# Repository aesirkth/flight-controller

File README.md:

# Flight Controller <!-- omit in toc -->

This is the embedded software on the Flight Controller for the project Mjollnir. The Flight Controller is on-board the rocket. The Flight Controller communicates with the ground through a radio link during all phases of the flight

The mission objectives for the Mjollnir project relevant to the electronics are the following:

**Primary objectives**

- **E.PO.1** Monitor the rocket while it is on the launchpad and give a “Go”/”No go” signal
- **E.PO.2** Control the rocket while it is on the launchpad
- **E.PO.3** Trigger the drogue parachute’s ejection after apogee
- **E.PO.4** Trigger the main parachute’s ejection before touchdown
- **E.PO.5** Support rocket recovery operations
- **E.PO.6** Record video footage from the rocket

**Secondary objectives**

- **E.SO.1** Send real-time telemetry from the rocket
- **E.SO.2** Receive & display real-time telemetry from the rocket at the Ground Station as long as the rocket is at a reasonable distance
- **E.SO.3** Send real-time video from the rocket
- **E.SO.4** Receive & display real-time video from the rocket at the Ground Station as long as the rocket is at a reasonable distance
- **E.SO.5** Acquire flight data with more sensors than those deemed “mission-critical”
- **E.SO.6** Store all flight data on-board the rocket for further analysis

All of them apply to some extent to the Flight Controller

# Table of content <!-- omit in toc -->

- [Description](#description)
  - [Hardware](#hardware)
  - [Software](#software)
    - [Installation](#installation)
  - [Tests](#tests)
- [Data protocol](#data-protocol)
- [Folder structure](#folder-structure)

# Description

## Hardware

The Flight Controller is a single PCB with power management, sensors, radio communication, and driver for the actuators used during the flight.

It has the following features:

- Dual microcontroller (main + backup)
- Low power long range LoRa transceiver
- Telemetry output via serial link (x3)
- GNSS support via serial link (x3)
- Compatible with 10 dof breakout board with MS5611 pressure sensors and MPU9250 IMU (2x)
- Compatible with K type thermocouples (2x)
- Flash memory
- EEDs driver for parachute ejection, with ESD protection + visual and audible warning (2x)
- RGB leds to display the board status
- Serial link to FPV transmitter
- CAN Bus

A more detailed description of the hardware is given in [doc/hardware_description.md](doc/hardware_description.md)

## Software

This repository uses [PlatformIO](https://platformio.org/) as the development tool for the two microcontrollers on the Flight Controller.

### Installation

1. Install [PlatformIO Core](https://docs.platformio.org/en/latest/core/index.html) or [PlatformIO IDE](https://platformio.org/install/ide) on your computer
2. Clone this repository
3. [Linux] install [udev](https://docs.platformio.org/en/latest/faq.html?highlight=99#platformio-udev-rules) rules

## Tests

See [test/](test/)

# Data protocol

The protocol to communicate between the Ground Station and the Rocket is detailed in [doc/data_protocol](doc/data_protocol.md)

# Folder structure

```
.
├── doc/
│   ├── img/
│   ├── diagrams/
│   ├── sources
│   |   └── flight_controller_v1.0.pdf
│   ├── data_protocol.md
│   └── hardware_description.md
├── include/
│   ├── hardware_definition_nano.h
│   └── hardware_definition_teensy.h
├── src/                                    // Code folder
│   └── test_companion_teensy.cpp           // Use with hardware_test_teensy
├── test/                                   // Unit tests
│   ├── hardware_test_nano/
│   ├── hardware_test_teensy/
│   └── README.md                           // Documentation for the tests
├── env_nano.ini                            // Extra platformIO config
├── env_teensy.ini                          // Extra platformIO config
├── LICENSE
├── platformio.ini                          // PlatformIO config
└── README.md                               // This file
```

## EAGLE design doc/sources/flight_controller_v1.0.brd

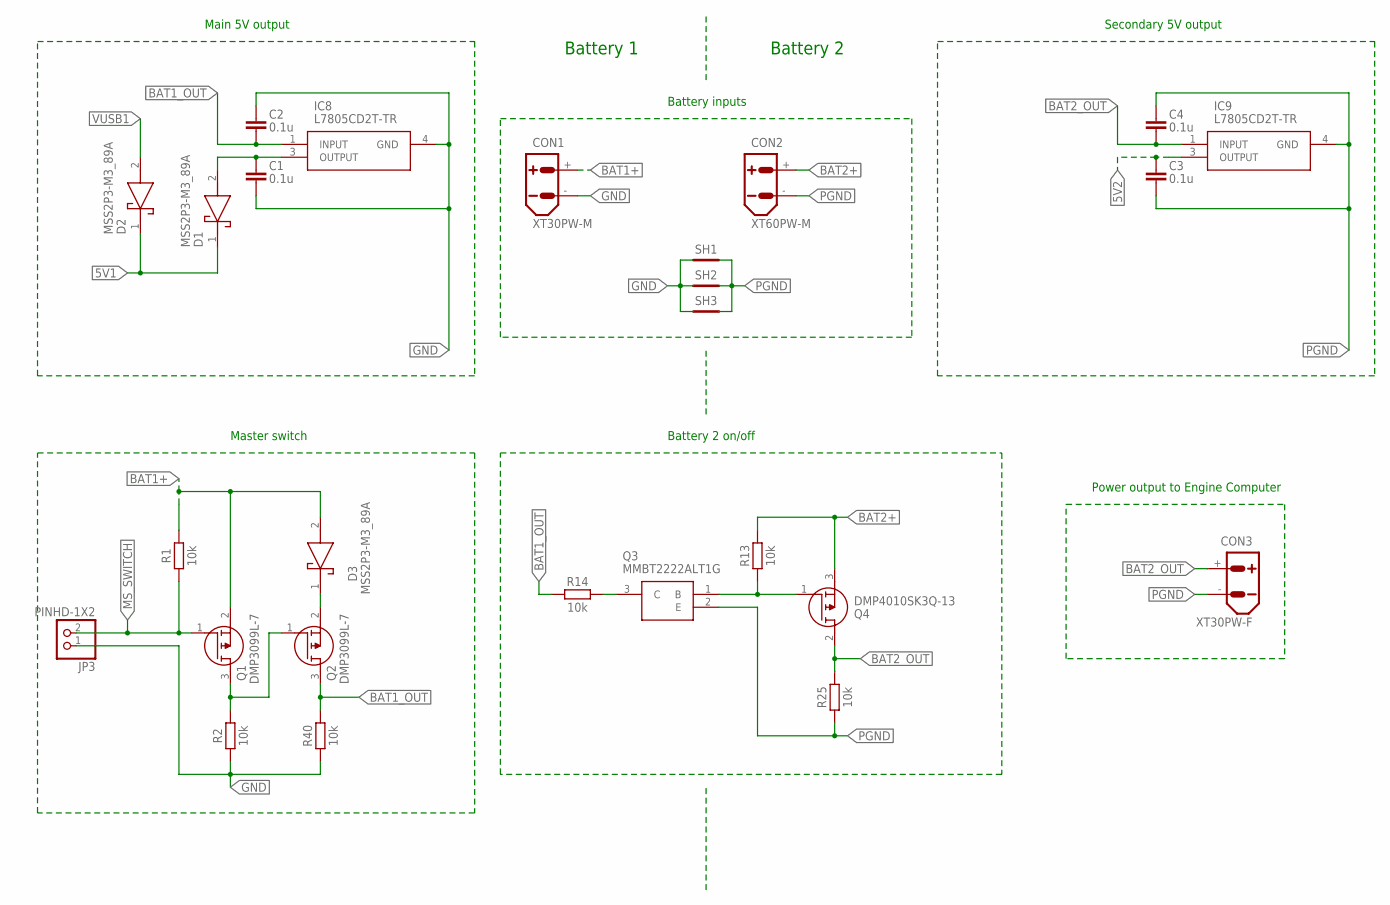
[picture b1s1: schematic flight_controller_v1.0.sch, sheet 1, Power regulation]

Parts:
C1, C2, C3, C4: 0.1u; CAPC2012X110
CON1: XT30PW-M
CON2: XT60PW-M
CON3: XT30PW-F
D1, D2, D3: MSS2P3-M3_89A; MSS2P3M389A
IC8, IC9: L7805CD2T-TR; TO254P1542X460-3N
JP3: PINHD-1X2; 1X02
Q1, Q2: DMP3099L-7; SOT96P240X120-3N
Q3: MMBT2222ALT1G; SOT96P237X111-3N
Q4: DMP4010SK3Q-13; SBR6100CTL13
R1, R2, R13, R14, R25, R40: 10k; RESC2012X65
SH1, SH2, SH3: SHORT-HT5; SHORT_TOP-50

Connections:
5V1: D1.1 (K), D2.1 (K); also elsewhere on the board
5V2: C3.1, IC9.3 (OUTPUT); also elsewhere on the board
BAT1+: CON1.+, D3.2 (A), Q1.2 (S), R1.2
BAT1_OUT: C2.2, IC8.1 (INPUT), Q2.3 (D), R14.1, R40.2; also elsewhere on the board
BAT2+: CON2.+, Q4.3 (S), R13.2
BAT2_OUT: C4.2, CON3.+, IC9.1 (INPUT), Q4.2 (D), R25.2; also elsewhere on the board
GND: C1.2, C2.1, CON1.-, IC8.4 (GND), JP3.1, R2.1, R40.1, SH1.1, SH2.1, SH3.1; also elsewhere on the board
MS_SWITCH: JP3.2, Q1.1 (G), R1.1; also elsewhere on the board
unnamed: Q1.3 (D), Q2.1 (G), R2.2
unnamed: Q3.1 (B), Q4.1 (G), R13.1
unnamed: Q3.3 (C), R14.2
unnamed: C1.1, D1.2 (A), IC8.3 (OUTPUT)
unnamed: D3.1 (K), Q2.2 (S)
PGND: C3.2, C4.1, CON2.-, CON3.-, IC9.4 (GND), Q3.2 (E), R25.1, SH1.2, SH2.2, SH3.2; also elsewhere on the board
VUSB1: D2.2 (A); also elsewhere on the board

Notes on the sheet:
Main 5V output
Battery inputs
Master switch
Secondary 5V output
Battery 2 on/off
Battery 1
Battery 2
Power output to Engine Computer

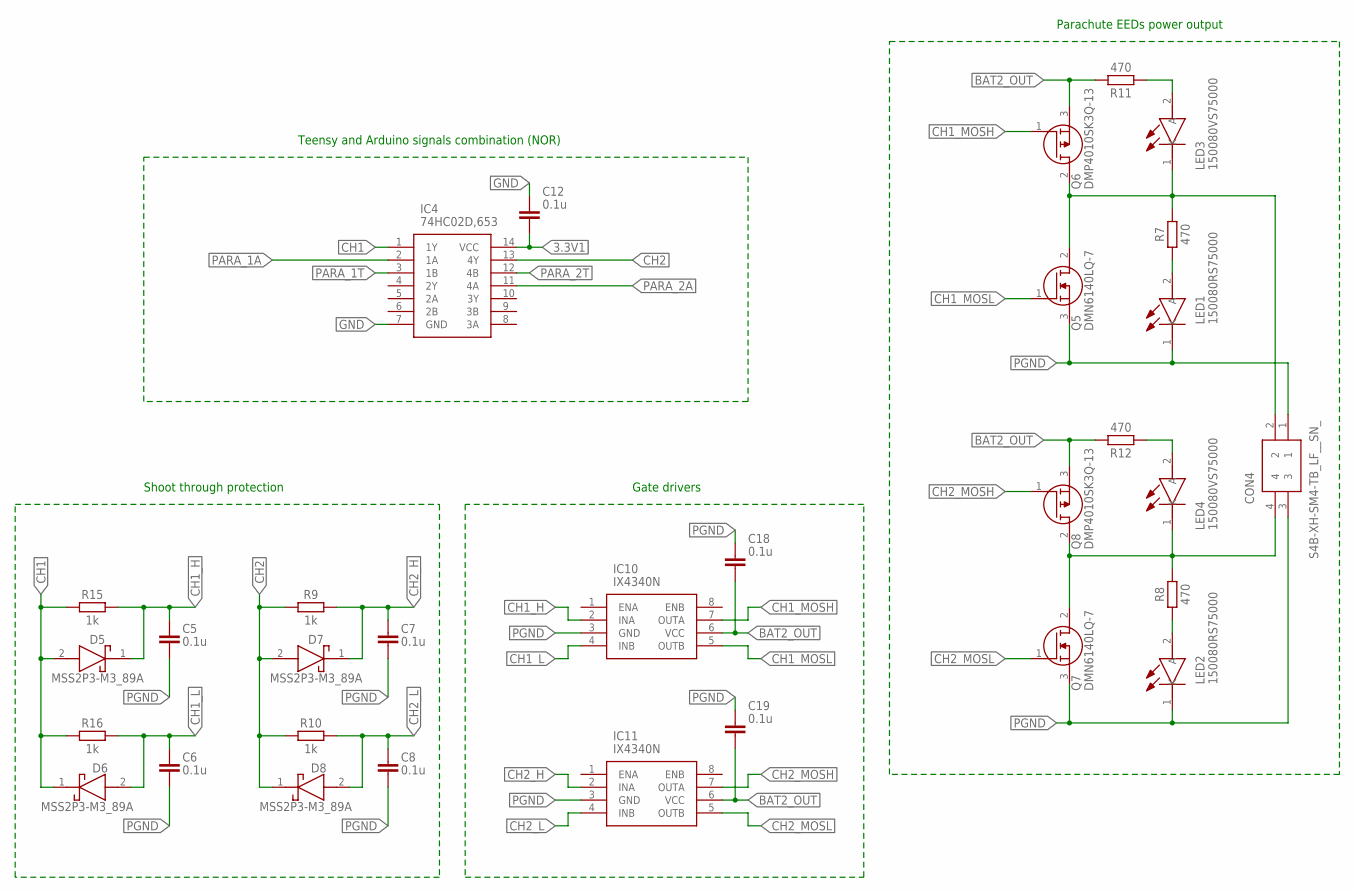
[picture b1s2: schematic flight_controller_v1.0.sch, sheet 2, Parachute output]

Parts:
C5, C6, C7, C8, C12, C18, C19: 0.1u; CAPC2012X110
CON4: S4B-XH-SM4-TB_LF__SN_; S4B-XH-SM4-TB
D5, D6, D7, D8: MSS2P3-M3_89A; MSS2P3M389A
IC4: 74HC02D,653; SOIC127P600X175-14N
IC10, IC11: IX4340N; SOIC127P600X175-8N
LED1, LED2: 150080RS75000; LEDC2012X80N
LED3, LED4: 150080VS75000; LEDC2012X80N
Q5, Q7: DMN6140LQ-7; SOT96P240X110-3N
Q6, Q8: DMP4010SK3Q-13; SBR6100CTL13
R7, R8, R11, R12: 470; RESC2012X65
R9, R10, R15, R16: 1k; RESC2012X65

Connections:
3.3V1: C12.2, IC4.14 (VCC); also elsewhere on the board
BAT2_OUT: C18.2, C19.2, IC10.6 (VCC), IC11.6 (VCC), Q6.3 (S), Q8.3 (S), R11.2, R12.2; also elsewhere on the board
CH1: D5.2 (A), D6.1 (K), IC4.1 (1Y), R15.1, R16.1
CH1_H: C5.1, D5.1 (K), IC10.2 (INA), R15.2
CH1_L: C6.1, D6.2 (A), IC10.4 (INB), R16.2
CH1_MOSH: IC10.7 (OUTA), Q6.1 (G)
CH1_MOSL: IC10.5 (OUTB), Q5.1 (G)
CH2: D7.2 (A), D8.1 (K), IC4.13 (4Y), R9.1, R10.1
CH2_H: C7.1, D7.1 (K), IC11.2 (INA), R9.2
CH2_L: C8.1, D8.2 (A), IC11.4 (INB), R10.2
CH2_MOSH: IC11.7 (OUTA), Q8.1 (G)
CH2_MOSL: IC11.5 (OUTB), Q7.1 (G)
GND: C12.1, IC4.7 (GND); also elsewhere on the board
unnamed: CON4.2, LED3.1 (K), Q5.2 (D), Q6.2 (D), R7.2
unnamed: LED1.2 (A), R7.1
unnamed: CON4.4, LED4.1 (K), Q7.2 (D), Q8.2 (D), R8.2
unnamed: LED2.2 (A), R8.1
unnamed: LED3.2 (A), R11.1
unnamed: LED4.2 (A), R12.1
PARA_1A: IC4.2 (1A); also elsewhere on the board
PARA_1T: IC4.3 (1B); also elsewhere on the board
PARA_2A: IC4.11 (4A); also elsewhere on the board
PARA_2T: IC4.12 (4B); also elsewhere on the board
PGND: C5.2, C6.2, C7.2, C8.2, C18.1, C19.1, CON4.1, CON4.3, IC10.3 (GND), IC11.3 (GND), LED1.1 (K), LED2.1 (K), Q5.3 (S), Q7.3 (S); also elsewhere on the board

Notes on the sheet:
Gate drivers
Parachute EEDs power output
Shoot through protection
Teensy and Arduino signals combination (NOR)

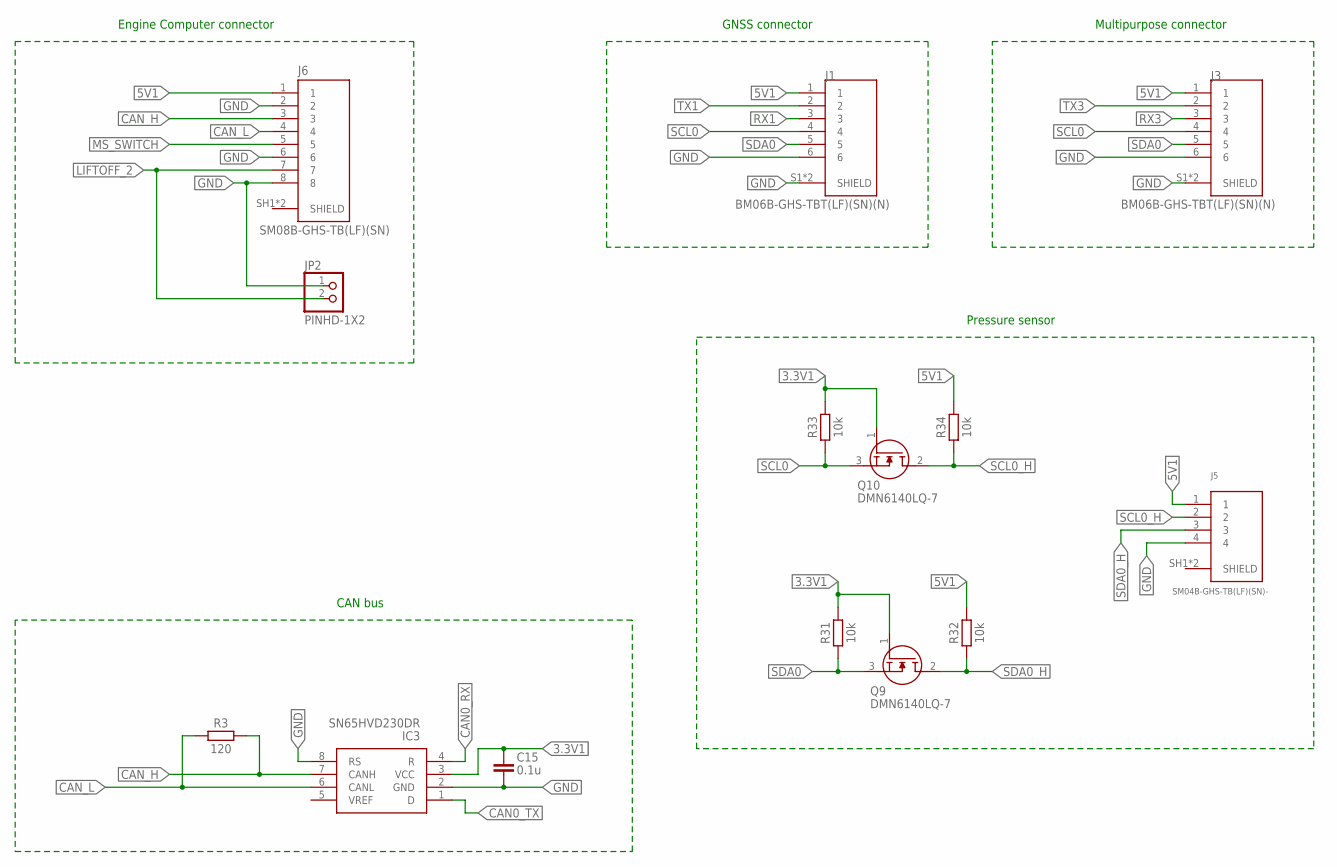
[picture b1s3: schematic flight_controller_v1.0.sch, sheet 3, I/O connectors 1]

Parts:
C15: 0.1u; CAPC2012X110
IC3: SN65HVD230DR; SOT127P600X175-8N
J1, J3: BM06B-GHS-TBT(LF)(SN)(N); JST_BM06B-GHS-TBT(LF)(SN)(N)
J5: SM04B-GHS-TB(LF)(SN)-; JST_SM04B-GHS-TB(LF)(SN)-
J6: SM08B-GHS-TB(LF)(SN); JST_SM08B-GHS-TB(LF)(SN)
JP2: PINHD-1X2; 1X02
Q9, Q10: DMN6140LQ-7; SOT96P240X110-3N
R3: 120; RESC2012X65
R31, R32, R33, R34: 10k; RESC2012X65

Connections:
3.3V1: C15.1, IC3.3 (VCC), Q9.1 (G), Q10.1 (G), R31.2, R33.2; also elsewhere on the board
5V1: J1.1, J3.1, J5.1, J6.1, R32.2, R34.2; also elsewhere on the board
CAN0_RX: IC3.4 (R); also elsewhere on the board
CAN0_TX: IC3.1 (D); also elsewhere on the board
CAN_H: IC3.7 (CANH), J6.3, R3.2
CAN_L: IC3.6 (CANL), J6.4, R3.1
GND: C15.2, IC3.2 (GND), IC3.8 (RS), J1.6, J1.S1 (SHIELD), J1.S2 (SHIELD), J3.6, J3.S1 (SHIELD), J3.S2 (SHIELD), J5.4, J6.2, J6.6, J6.8, JP2.1; also elsewhere on the board
LIFTOFF_2: J6.7, JP2.2; also elsewhere on the board
MS_SWITCH: J6.5; also elsewhere on the board
RX1: J1.3; also elsewhere on the board
RX3: J3.3; also elsewhere on the board
SCL0: J1.4, J3.4, Q10.3 (S), R33.1; also elsewhere on the board
SCL0_H: J5.2, Q10.2 (D), R34.1
SDA0: J1.5, J3.5, Q9.3 (S), R31.1; also elsewhere on the board
SDA0_H: J5.3, Q9.2 (D), R32.1
SHIELD: J5.SH1 (SHIELD), J5.SH2 (SHIELD)
TX1: J1.2; also elsewhere on the board
TX3: J3.2; also elsewhere on the board

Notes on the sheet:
CAN bus
GNSS connector
Engine Computer connector
Multipurpose connector
Pressure sensor

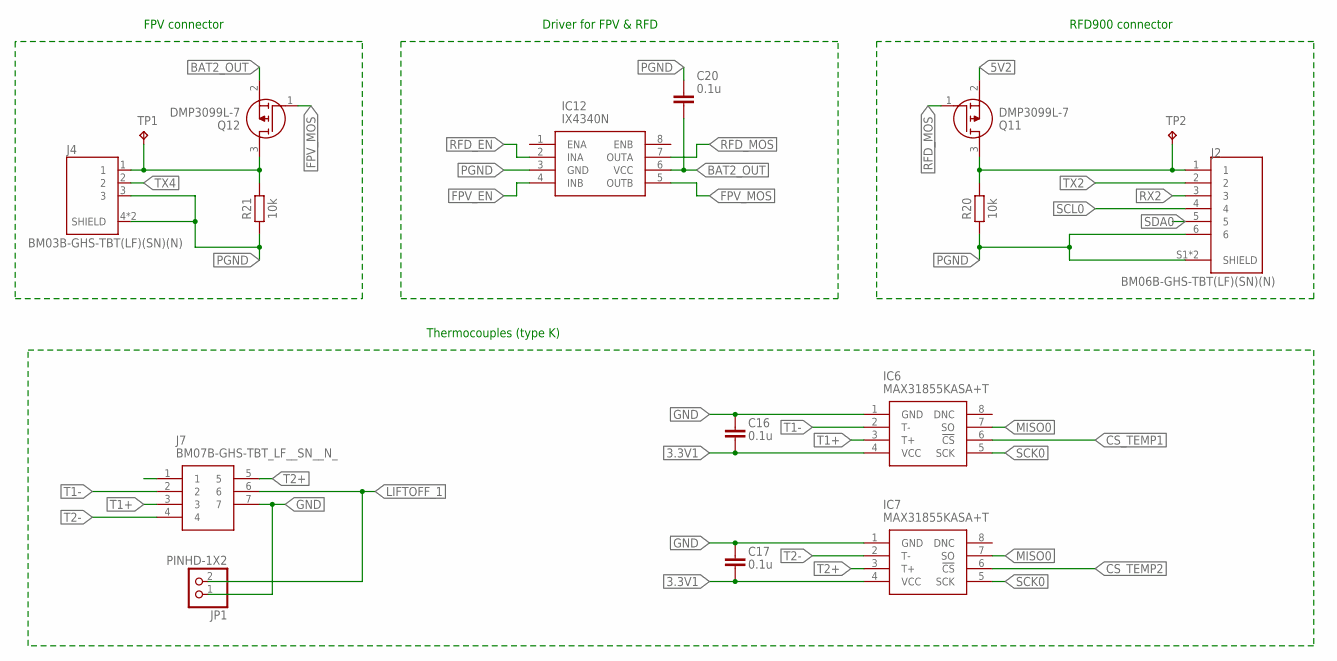
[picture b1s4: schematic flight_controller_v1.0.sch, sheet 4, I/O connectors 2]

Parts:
C16, C17, C20: 0.1u; CAPC2012X110
IC6, IC7: MAX31855KASA+T; SOIC127P600X175-8N
IC12: IX4340N; SOIC127P600X175-8N
J2: BM06B-GHS-TBT(LF)(SN)(N); JST_BM06B-GHS-TBT(LF)(SN)(N)
J4: BM03B-GHS-TBT(LF)(SN)(N); CONN_BM03B-GHS-TBT(LF)(SN)(N)
J7: BM07B-GHS-TBT_LF__SN__N_; BM07B-GHS-TBT
JP1: PINHD-1X2; 1X02
Q11, Q12: DMP3099L-7; SOT96P240X120-3N
R20, R21: 10k; RESC2012X65
TP1, TP2: TPB1,27; B1,27

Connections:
3.3V1: C16.2, C17.2, IC6.4 (VCC), IC7.4 (VCC); also elsewhere on the board
5V2: Q11.2 (S); also elsewhere on the board
BAT2_OUT: C20.2, IC12.6 (VCC), Q12.2 (S); also elsewhere on the board
CS_TEMP1: IC6.6 (!CS); also elsewhere on the board
CS_TEMP2: IC7.6 (!CS); also elsewhere on the board
FPV_EN: IC12.4 (INB); also elsewhere on the board
FPV_MOS: IC12.5 (OUTB), Q12.1 (G)
GND: C16.1, C17.1, IC6.1 (GND), IC7.1 (GND), J7.7, JP1.1; also elsewhere on the board
LIFTOFF_1: J7.6, JP1.2; also elsewhere on the board
MISO0: IC6.7 (SO), IC7.7 (SO); also elsewhere on the board
unnamed: J2.1, Q11.3 (D), R20.2, TP2.TP
unnamed: J4.1, Q12.3 (D), R21.2, TP1.TP
PGND: C20.1, IC12.3 (GND), J2.6, J2.S1 (SHIELD), J2.S2 (SHIELD), J4.3, J4.4 (SHIELD), J4.5 (SHIELD), R20.1, R21.1; also elsewhere on the board
RFD_EN: IC12.2 (INA); also elsewhere on the board
RFD_MOS: IC12.7 (OUTA), Q11.1 (G)
RX2: J2.3; also elsewhere on the board
SCK0: IC6.5 (SCK), IC7.5 (SCK); also elsewhere on the board
SCL0: J2.4; also elsewhere on the board
SDA0: J2.5; also elsewhere on the board
T1+: IC6.3 (T+), J7.3
T1-: IC6.2 (T-), J7.2
T2+: IC7.3 (T+), J7.5
T2-: IC7.2 (T-), J7.4
TX2: J2.2; also elsewhere on the board
TX4: J4.2; also elsewhere on the board

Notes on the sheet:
FPV connector
Driver for FPV & RFD
RFD900 connector
Thermocouples (type K)

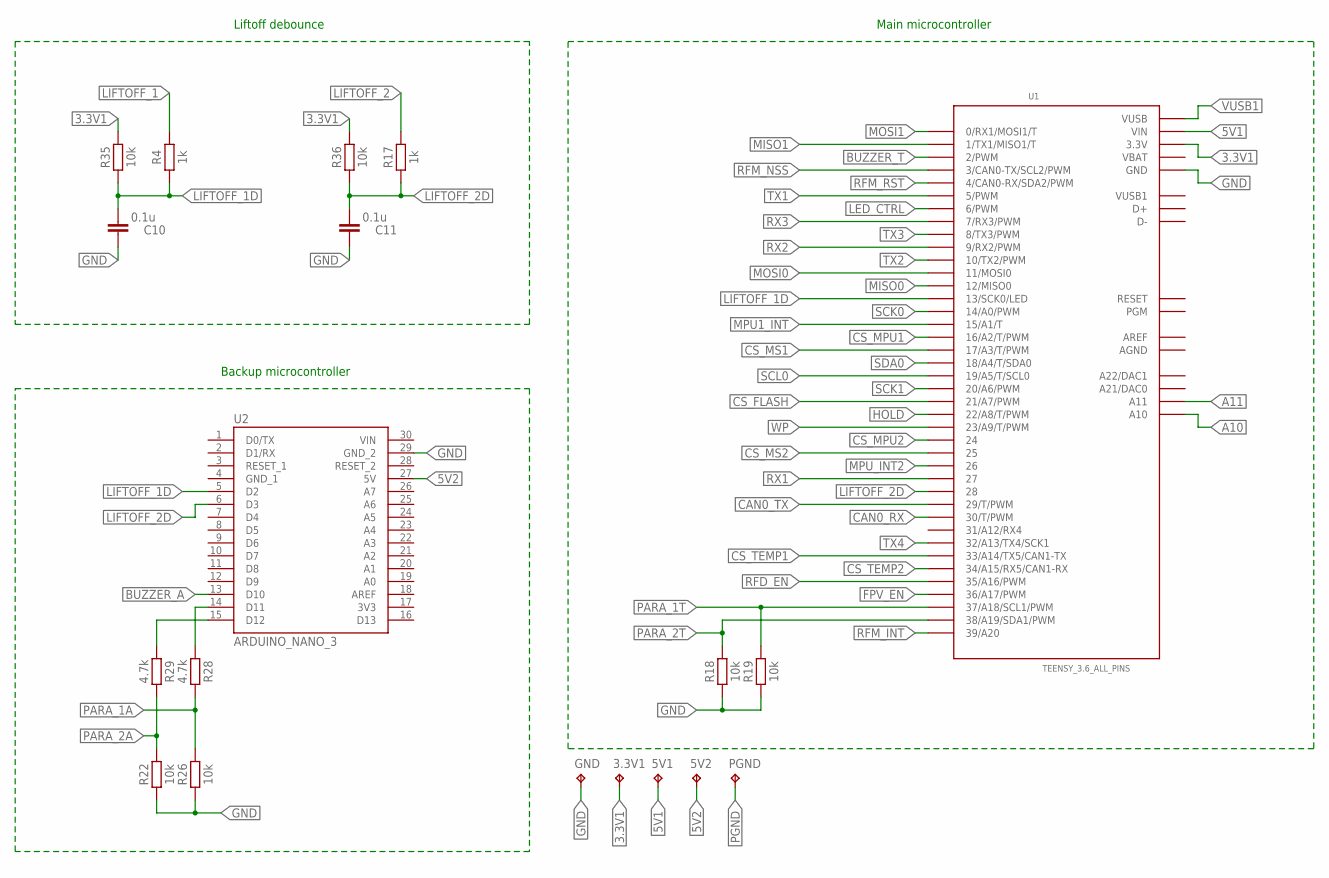
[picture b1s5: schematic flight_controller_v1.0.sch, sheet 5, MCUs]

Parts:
3.3V1, 5V1, 5V2: TPB1,27; B1,27
C10, C11: 0.1u; CAPC2012X110
GND: TPB1,27; B1,27
PGND: TPB1,27; B1,27
R4, R17: 1k; RESC2012X65
R18, R19, R22, R26, R35, R36: 10k; RESC2012X65
R28, R29: 4.7k; RESC2012X65
U1: TEENSY_3.6_ALL_PINS
U2: ARDUINO_NANO_3; MODULE_A000005

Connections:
3.3V1: 3.3V1.TP, R35.2, R36.2, U1.3.3V, U1.3.3V3 (3.3V), U1.3.3V4 (3.3V); also elsewhere on the board
3V3: U2.17 (3V3)
5V1: 5V1.TP, U1.VIN; also elsewhere on the board
5V2: 5V2.TP, U2.27 (5V); also elsewhere on the board
A10: U1.A10; also elsewhere on the board
A11: U1.A11; also elsewhere on the board
AGND: U1.AGND
AREF: U1.AREF
BUZZER_A: U2.13 (D10); also elsewhere on the board
BUZZER_T: U1.2 (2/PWM); also elsewhere on the board
CAN0_RX: U1.30 (30/T/PWM); also elsewhere on the board
CAN0_TX: U1.29 (29/T/PWM); also elsewhere on the board
CS_FLASH: U1.21/A7 (21/A7/PWM); also elsewhere on the board
CS_MPU1: U1.16/A2 (16/A2/T/PWM); also elsewhere on the board
CS_MPU2: U1.24; also elsewhere on the board
CS_MS1: U1.17/A3 (17/A3/T/PWM); also elsewhere on the board
CS_MS2: U1.25; also elsewhere on the board
CS_TEMP1: U1.33/A14 (33/A14/TX5/CAN1-TX); also elsewhere on the board
CS_TEMP2: U1.34/A15 (34/A15/RX5/CAN1-RX); also elsewhere on the board
FPV_EN: U1.36/A17 (36/A17/PWM); also elsewhere on the board
GND: C10.2, C11.2, GND.TP, R18.1, R19.1, R22.1, R26.1, U1.GND, U1.GND1 (GND), U1.GND3 (GND), U1.GND4 (GND), U1.GND6 (GND), U2.29 (GND_2); also elsewhere on the board
GND_1: U2.4 (GND_1)
HOLD: U1.22/A8 (22/A8/T/PWM); also elsewhere on the board
LED_CTRL: U1.6 (6/PWM); also elsewhere on the board
LIFTOFF_1: R4.2; also elsewhere on the board
LIFTOFF_1D: C10.1, R4.1, R35.1, U1.13 (13/SCK0/LED), U2.5 (D2)
LIFTOFF_2: R17.2; also elsewhere on the board
LIFTOFF_2D: C11.1, R17.1, R36.1, U1.28, U2.6 (D3)
MISO0: U1.12 (12/MISO0); also elsewhere on the board
MISO1: U1.1 (1/TX1/MISO1/T); also elsewhere on the board
MOSI0: U1.11 (11/MOSI0); also elsewhere on the board
MOSI1: U1.0 (0/RX1/MOSI1/T); also elsewhere on the board
MPU1_INT: U1.15/A1 (15/A1/T); also elsewhere on the board
MPU_INT2: U1.26; also elsewhere on the board
unnamed: R28.1, U2.14 (D11)
unnamed: R29.1, U2.15 (D12)
PARA_1A: R26.2, R28.2; also elsewhere on the board
PARA_1T: R19.2, U1.37/A18 (37/A18/SCL1/PWM); also elsewhere on the board
PARA_2A: R22.2, R29.2; also elsewhere on the board
PARA_2T: R18.2, U1.38/A19 (38/A19/SDA1/PWM); also elsewhere on the board
PGND: PGND.TP; also elsewhere on the board
RFD_EN: U1.35/A16 (35/A16/PWM); also elsewhere on the board
RFM_INT: U1.39/A20; also elsewhere on the board
RFM_NSS: U1.3 (3/CAN0-TX/SCL2/PWM); also elsewhere on the board
RFM_RST: U1.4 (4/CAN0-RX/SDA2/PWM); also elsewhere on the board
RX1: U1.27; also elsewhere on the board
RX2: U1.9 (9/RX2/PWM); also elsewhere on the board
RX3: U1.7 (7/RX3/PWM); also elsewhere on the board
SCK0: U1.14/A0 (14/A0/PWM); also elsewhere on the board
SCK1: U1.20/A6 (20/A6/PWM); also elsewhere on the board
SCL0: U1.19/A5 (19/A5/T/SCL0); also elsewhere on the board
SDA0: U1.18/A4 (18/A4/T/SDA0); also elsewhere on the board
TX1: U1.5 (5/PWM); also elsewhere on the board
TX2: U1.10 (10/TX2/PWM); also elsewhere on the board
TX3: U1.8 (8/TX3/PWM); also elsewhere on the board
TX4: U1.32/A13 (32/A13/TX4/SCK1); also elsewhere on the board
VBAT: U1.VBAT
VIN: U2.30 (VIN)
VUSB1: U1.VUSB, U1.VUSB1; also elsewhere on the board
WP: U1.23/A9 (23/A9/T/PWM); also elsewhere on the board

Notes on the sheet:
Main microcontroller
Backup microcontroller
Liftoff debounce

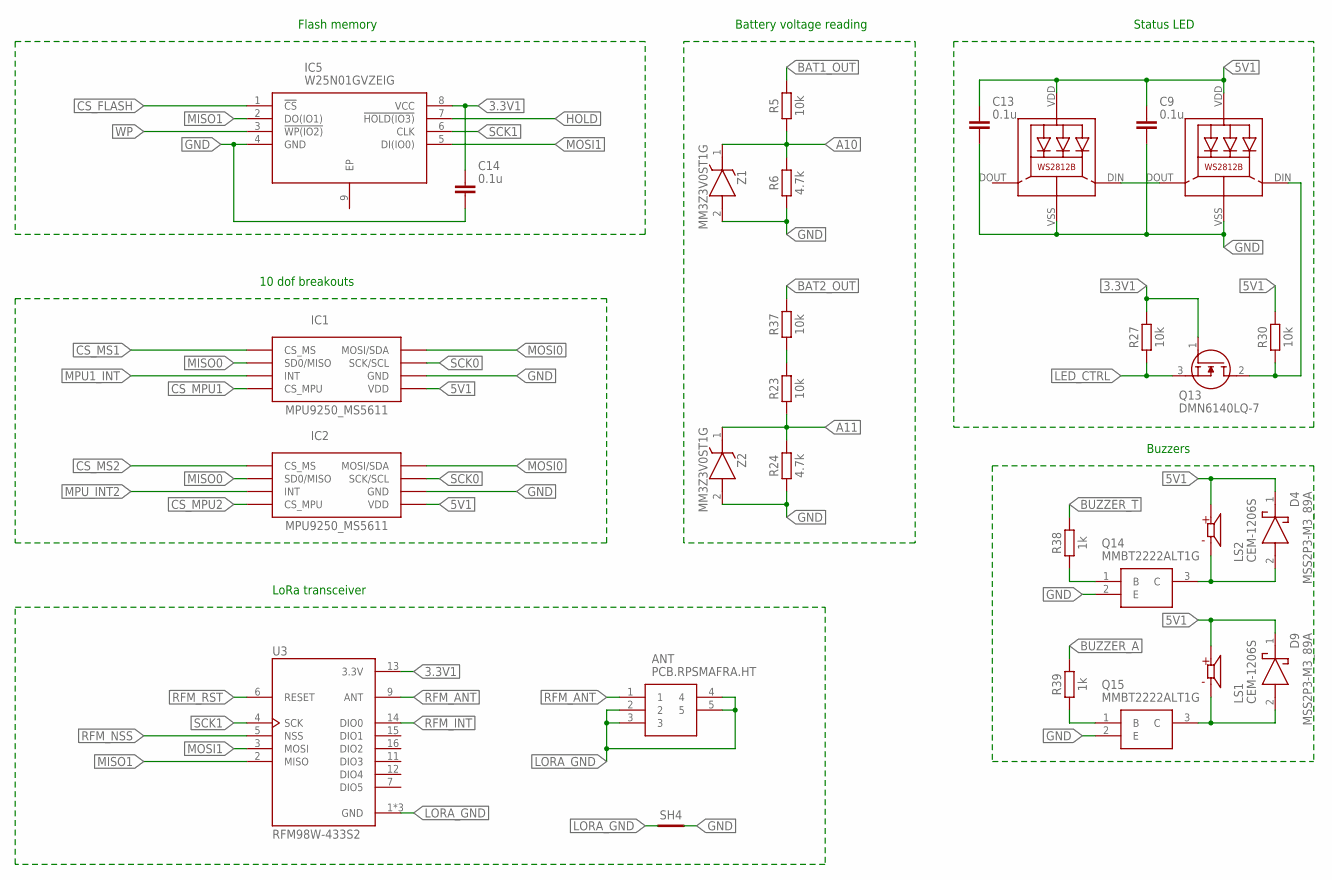
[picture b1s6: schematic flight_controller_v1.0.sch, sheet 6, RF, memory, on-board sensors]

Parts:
ANT: PCB.RPSMAFRA.HT; PCBRPSMAFRAHT
C9, C13, C14: 0.1u; CAPC2012X110
D4, D9: MSS2P3-M3_89A; MSS2P3M389A
IC1, IC2: MPU9250_MS5611; 2X4PIN
IC5: W25N01GVZEIG; SON127P800X600X80-9N
LED5, LED6: WS2812B
LS1, LS2: CEM-1206S; CUI_CEM-1206S
Q13: DMN6140LQ-7; SOT96P240X110-3N
Q14, Q15: MMBT2222ALT1G; SOT96P237X111-3N
R5, R23, R27, R30, R37: 10k; RESC2012X65
R6, R24: 4.7k; RESC2012X65
R38, R39: 1k; RESC2012X65
SH4: SHORT-HT5; SHORT_TOP-50
U3: RFM98W-433S2; XCVR_RFM98W-433S2
Z1, Z2: MM3Z3V0ST1G; SOD2512X110N

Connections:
3.3V1: C14.1, IC5.8 (VCC), Q13.1 (G), R27.2, U3.13 (3.3V); also elsewhere on the board
5V1: C9.1, C13.1, D4.1 (K), D9.1 (K), IC1.P$5 (VDD), IC2.P$5 (VDD), LED5.VDD, LED6.VDD, LS1.P, LS2.P, R30.2; also elsewhere on the board
A10: R5.1, R6.2, Z1.1 (K); also elsewhere on the board
A11: R23.1, R24.2, Z2.1 (K); also elsewhere on the board
BAT1_OUT: R5.2; also elsewhere on the board
BAT2_OUT: R37.2; also elsewhere on the board
BUZZER_A: R39.2; also elsewhere on the board
BUZZER_T: R38.2; also elsewhere on the board
CS_FLASH: IC5.1 (!CS); also elsewhere on the board
CS_MPU1: IC1.P$4 (CS_MPU); also elsewhere on the board
CS_MPU2: IC2.P$4 (CS_MPU); also elsewhere on the board
CS_MS1: IC1.P$1 (CS_MS); also elsewhere on the board
CS_MS2: IC2.P$1 (CS_MS); also elsewhere on the board
GND: C9.2, C13.2, C14.2, IC1.P$6 (GND), IC2.P$6 (GND), IC5.4 (GND), LED5.VSS (GND), LED6.VSS (GND), Q14.2 (E), Q15.2 (E), R6.1, R24.1, SH4.2, Z1.2 (A), Z2.2 (A); also elsewhere on the board
HOLD: IC5.7 (!HOLD(IO3)); also elsewhere on the board
LED_CTRL: Q13.3 (S), R27.1; also elsewhere on the board
LORA_GND: ANT.2, ANT.3, ANT.4, ANT.5, SH4.1, U3.1 (GND), U3.8 (GND), U3.10 (GND)
MISO0: IC1.P$2 (SD0/MISO), IC2.P$2 (SD0/MISO); also elsewhere on the board
MISO1: IC5.2 (DO(IO1)), U3.2 (MISO); also elsewhere on the board
MOSI0: IC1.P$8 (MOSI/SDA), IC2.P$8 (MOSI/SDA); also elsewhere on the board
MOSI1: IC5.5 (DI(IO0)), U3.3 (MOSI); also elsewhere on the board
MPU1_INT: IC1.P$3 (INT); also elsewhere on the board
MPU_INT2: IC2.P$3 (INT); also elsewhere on the board
unnamed: LED5.DOUT (DO), LED6.DIN (DI)
unnamed: LED5.DIN (DI), Q13.2 (D), R30.1
unnamed: R23.2, R37.1
unnamed: D4.2 (A), LS2.N, Q14.3 (C)
unnamed: Q14.1 (B), R38.1
unnamed: D9.2 (A), LS1.N, Q15.3 (C)
unnamed: Q15.1 (B), R39.1
RFM_ANT: ANT.1, U3.9 (ANT)
RFM_INT: U3.14 (DIO0); also elsewhere on the board
RFM_NSS: U3.5 (NSS); also elsewhere on the board
RFM_RST: U3.6 (RESET); also elsewhere on the board
SCK0: IC1.P$7 (SCK/SCL), IC2.P$7 (SCK/SCL); also elsewhere on the board
SCK1: IC5.6 (CLK), U3.4 (SCK); also elsewhere on the board
WP: IC5.3 (!WP(IO2)); also elsewhere on the board

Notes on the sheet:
Flash memory
LoRa transceiver
10 dof breakouts
Battery voltage reading
Status LED
Buzzers

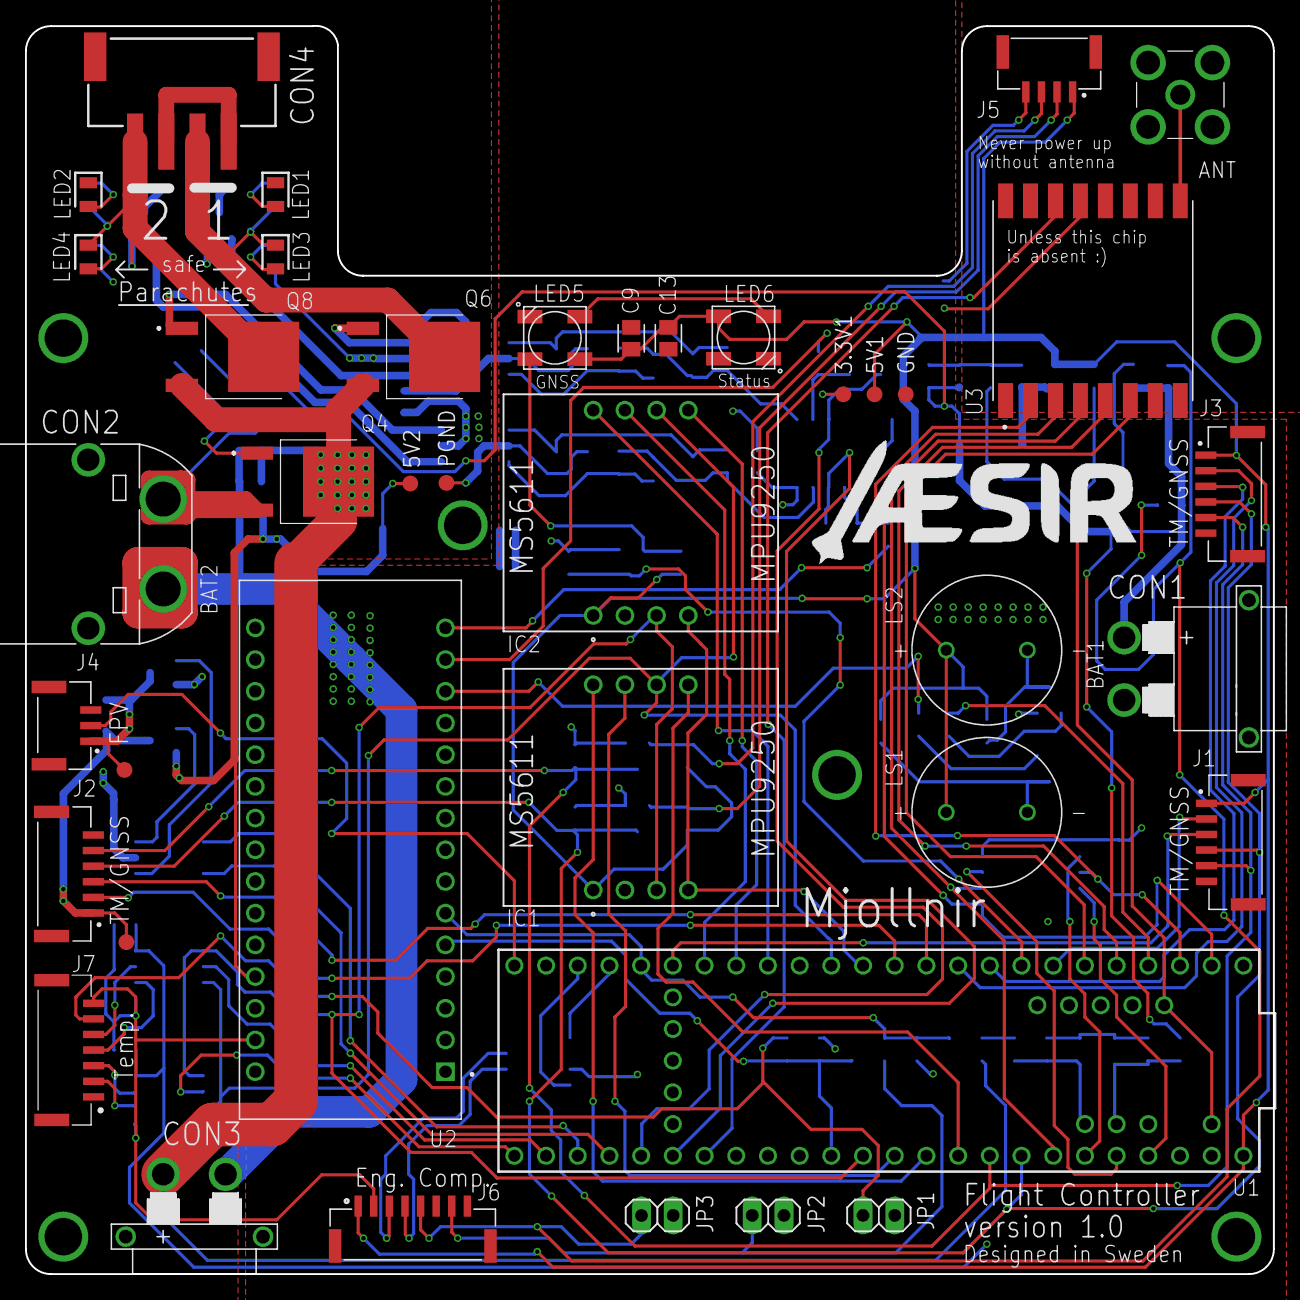
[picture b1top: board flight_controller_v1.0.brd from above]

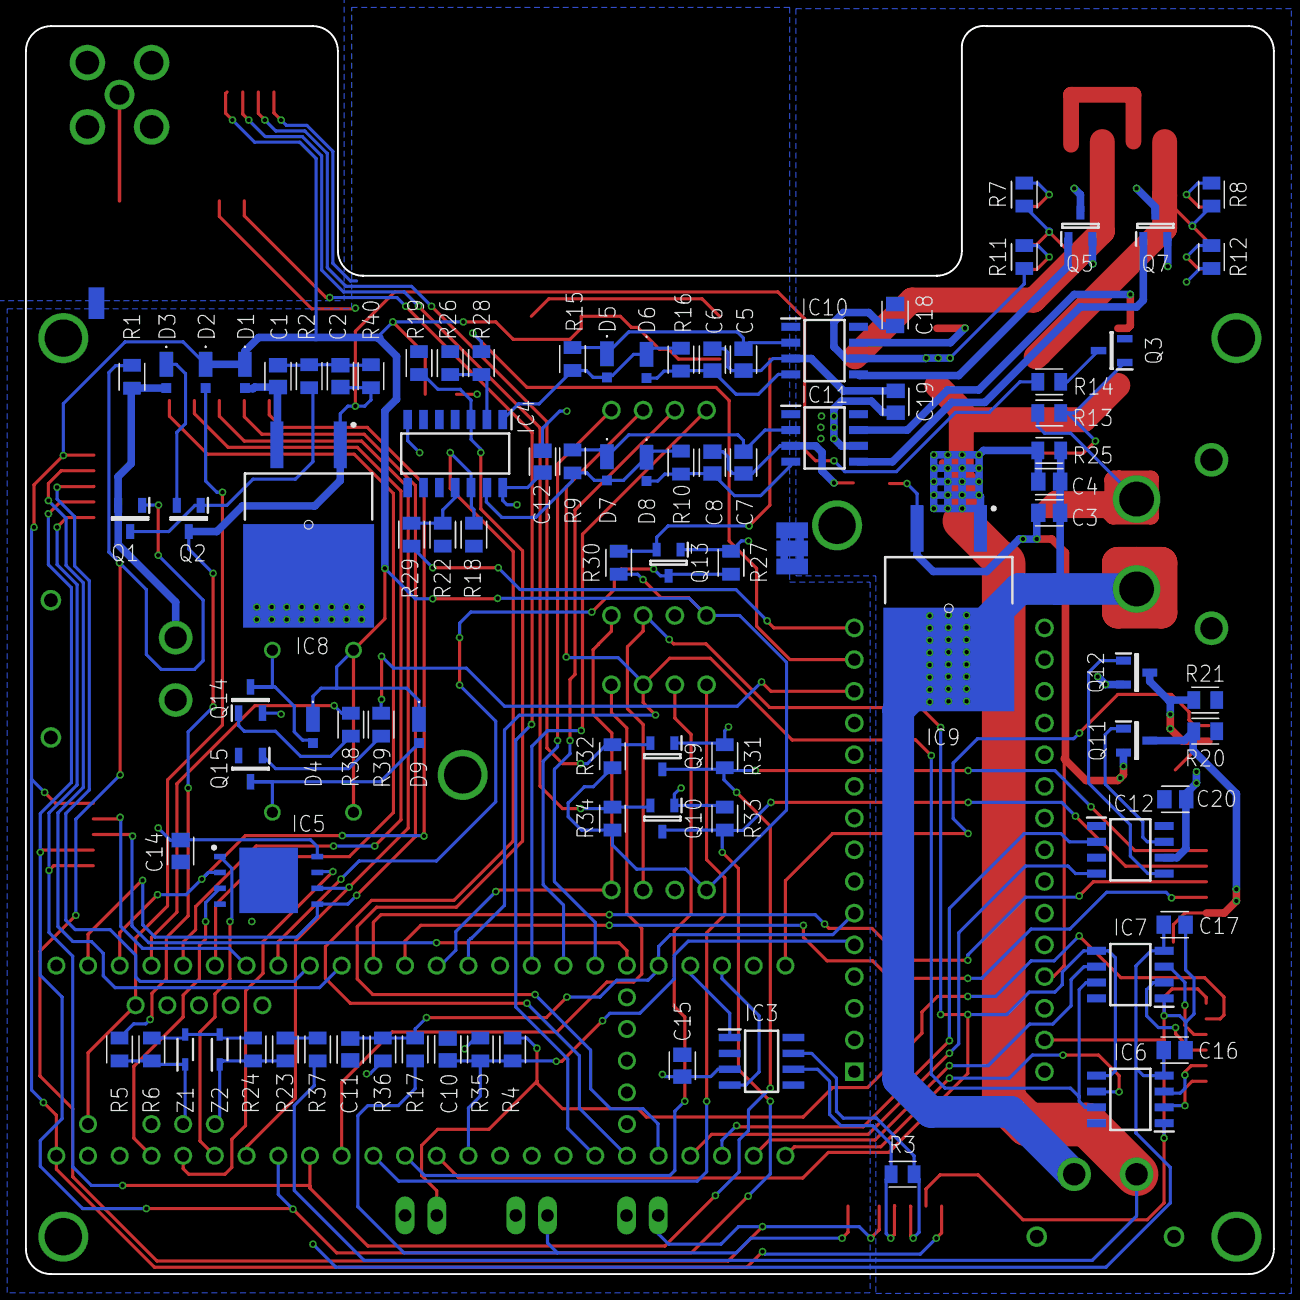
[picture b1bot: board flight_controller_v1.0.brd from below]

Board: 4 copper layers, 100.0 x 100.0 mm, 135 parts (95 on the bottom side), 102 nets.

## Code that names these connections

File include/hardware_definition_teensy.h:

/* Pin definition for the Teensy */
#define PIN_FPV_DIS PIN_J4_DIS
#define PIN_RFD_DIS PIN_J2_DIS

#define PIN_MOSI1 0
#define PIN_MISO1 1
#define PIN_BUZZER 2
#define PIN_RFM_NSS 3
#define PIN_RFM_RST 4
#define PIN_TX1 5
#define PIN_LED_CTRL 6
#define PIN_RX3 7
#define PIN_TX3 8
#define PIN_RX2 9
#define PIN_TX2 10
#define PIN_MOSI0 11
#define PIN_MISO0 12
#define PIN_LIFTOFF1 13
#define PIN_SCK0 14
#define PIN_MPU1_INT 15
#define PIN_CS_MPU1 16
#define PIN_CS_MS1 17
#define PIN_SDA0 18
#define PIN_SCL0 19
#define PIN_SCK1 20
#define PIN_CS_FLASH 21
#define PIN_HOLD 22
#define PIN_WP 23
#define PIN_CS_MPU2 24
#define PIN_CS_MS2 25
#define PIN_MPU_INT2 26
#define PIN_RX1 27
#define PIN_LIFTOFF2 28
#define PIN_CAN0_TX 29
#define PIN_CAN0_RX 30
#define PIN_RX4 31
#define PIN_TX4 32
#define PIN_CS_TEMP1 33
#define PIN_CS_TEMP2 34
#define PIN_J2_DIS 35
#define PIN_J4_DIS 36
#define PIN_PARA1 37
#define PIN_PARA2 38
#define PIN_RFM_INT 39
#define PIN_BAT1 A10
#define PIN_BAT2 A11

/* Port definition for the Teensy */
#define PORT_MPU1 SPI
#define PORT_MPU2 SPI
#define PORT_MS1 SPI
#define PORT_MS2 SPI
#define PORT_RFM SPI1

/* Other definitions */
#define NUM_RGB_LEDS 2
#define BUZZER_FREQ 2400  // Hz
#define RFM_FREQ 434.0f
#define RFM_TX_POWER 13 //legal max

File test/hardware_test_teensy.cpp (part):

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#define RFM_SPI hardware_spi1

// Adafruit_NeoPixel strip = Adafruit_NeoPixel(RGB_LEDS_NUM, RGB_LEDS_PIN, NEO_GRB + NEO_KHZ800); // Seems not to work at 800 kHz
Adafruit_NeoPixel strip = Adafruit_NeoPixel(NUM_RGB_LEDS, PIN_LED_CTRL, NEO_GRB + NEO_KHZ400);

MS5611 ms1(PIN_CS_MS1, PORT_MS1, MS5611_MAX_SPI_FREQ);
MS5611 ms2(PIN_CS_MS2, PORT_MS2, MS5611_MAX_SPI_FREQ);

FlexCAN CANbus(1000000, 0, 1, 1);  // 1Mbs, CAN0, pins 29&30 for TX&RX
static CAN_message_t msg;

RH_RF95 rfm(PIN_RFM_NSS, digitalPinToInterrupt(PIN_RFM_INT), RFM_SPI);

void setup() {
  delay(2000);  // Required to make the unit tests work
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  Serial3.setRX(PIN_RX3);
  Serial3.setTX(PIN_TX3);

  SPI.setMOSI(PIN_MOSI0);
  SPI.setMISO(PIN_MISO0);
  SPI.setSCK(PIN_SCK0);

  SPI1.setMOSI(PIN_MOSI1);
  SPI1.setMISO(PIN_MISO1);
  SPI1.setSCK(PIN_SCK1);

  // Set I/O
  pinMode(PIN_PARA1, OUTPUT);
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  digitalWrite(PIN_PARA1, LOW);  // LOW means inactive parachute
  digitalWrite(PIN_PARA2, LOW);  // LOW means inactive parachute

  pinMode(PIN_RFD_EN, OUTPUT);
  pinMode(PIN_FPV_EN, OUTPUT);
  digitalWrite(PIN_RFD_EN, LOW);  // LOW means active Telemetry output
  digitalWrite(PIN_FPV_EN, LOW);

  UNITY_BEGIN();

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*/
void test_RFM() {
  // Hard-reset the chip
  pinMode(PIN_RFM_RST, OUTPUT);
  digitalWrite(PIN_RFM_RST, HIGH);
  delay(100);
  digitalWrite(PIN_RFM_RST, LOW);
  delay(10);
  digitalWrite(PIN_RFM_RST, HIGH);
  delay(100);

  TEST_ASSERT_TRUE(rfm.init());
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  TEST_MESSAGE("It should turn off for 1s, do you see it ?");
  TEST_MESSAGE("(Measure the voltage on the test pad, 5V expected)");
  delay(1000);
  digitalWrite(PIN_RFD_EN, HIGH);
  delay(1000);
  digitalWrite(PIN_RFD_EN, LOW);

  TEST_PASS_MESSAGE("Test passed if saw it");
}
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  TEST_MESSAGE("It should turn off for 1s, do you see it ?");
  TEST_MESSAGE("(Measure the voltage on the test pad, 12V expected)");
  delay(1000);
  digitalWrite(PIN_FPV_EN, HIGH);
  delay(1000);
  digitalWrite(PIN_FPV_EN, LOW);

  TEST_PASS_MESSAGE("Test passed if saw it");
}
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
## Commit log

2020-08-03 doc: brief description
2020-08-03 add LICENSE
2020-08-03 doc: microcontrollers and battery inputs
2020-08-03 doc: more detailed hardware description
2020-08-03 doc: update pictures
2020-08-03 doc: center images
2020-08-05 doc: add mission objectives
2020-08-13 add TC overview
2020-08-13 add telemetry overview
2020-08-13 typo
2020-08-15 doc: update communication sequences
2020-08-15 add definition for commands to FC
2020-08-15 update ID allocation
2020-08-15 leave frame IDs non allocated for future use
2020-08-15 compress xml files
2020-08-16 Fix ID allocation for Engine Computer TM
2020-08-16 convert big table to HTML
2020-08-16 add considerations about time stamps
2020-08-16 add placeholder for time sync frame
2020-08-16 add telemetry data description
2020-08-16 add explainer for tables and xml
2020-08-16 update table formating
2020-08-16 fix details
2020-09-03 add engine computer TC
2020-09-03 add note for remaining ID values
2020-09-03 add a note about diagrams.net
2020-09-03 rewrite note on time stamps
2020-09-04 apply phrasing suggestions from @eweilow
2020-09-05 replace 'sleep mode' with 'power mode'
2020-09-05 use 'set' in commands names
2020-09-05 add hardware tests
2020-09-05 add software description
2020-09-05 add serial test
2020-09-05 add description for test file
2020-09-05 make test companion work on J1, J2, J3
2020-09-05 add comments to test file
2020-09-05 add description to test_companion_teensy
2020-09-05 doc: update test README
2020-09-05 update defines for J2 and J4
2020-09-05 add unit tests for arduino nano
2020-09-05 doc: link to the test folder
2020-09-05 doc: update folder structure
2020-09-05 doc: describe power setup
2020-09-05 doc: add board capabilities overview
2020-09-05 doc: add connectors
2020-09-05 doc: add purpose of FC v1.0
2020-09-05 doc: fix omega symbol
2020-09-05 doc: rename data_protocol file
2020-09-05 doc: describe FC chips
2020-09-05 doc: a word on parachute drivers
2020-09-05 add eagle source files
2020-10-25 Stratospheric Balloon Project dev branch
2020-10-25 Expanded data_protocol.md telemetry section
2020-11-03 GPS support and minor tweaks to data_protocol.h
2020-11-03 Corrections on GNSS time and data
2020-11-05 Ver 0.1
2020-11-28 Data protocol description updated
2020-11-28 Update README.md
    Link broken to data_protocol documentation
2020-12-16 Started working on implementation of RadioHead lib
2020-12-27 Add nmea parser
2020-12-28 Basic example of Flash Memory operation. Started implementation of dedicated library
2020-12-28 Basic read functions work. Added check for factory bad blocks identification
2020-12-28 Added support for reading BBM LUT
2020-12-29 fix dependencies
2020-12-29 rename files
2021-01-26 Implemented library for SPI1
2021-01-27 fix examples
2021-01-30 Writing error figured out. https://stackoverflow.com/a/44551298
2021-02-05 clean up
2021-02-09 Finally working
2021-02-23 Removed unnecesary comments
2021-02-25 remove engine stuff, add time, add flash
2021-02-25 small fixes
2021-02-25 Update doc/data_protocol.md
    typo
2021-02-27 update ranges
2021-02-27 update GNSS data
2021-03-02 update gps, data protocol, telecommand
2021-03-16 add handshake
2021-03-16 replace libraries with local version, work on main loop, protocol generation
2021-03-18 implement code generation
2021-03-26 update codegen
2021-03-26 Add limits to radiohead
2021-03-26 Created environment and started implementing relay code.
2021-03-26 Started implementing relay code; not yet tested
2021-03-28 fix error checking
2021-03-28 Add Edda relaying, update codegen
2021-04-12 preliminary DMA
2021-04-13 better structure
2021-04-13 Relay working decently
2021-04-13 update DataProtocol, relay handshake
2021-04-13 update codegen and DataProtocol
2021-04-19 Update flash chip lib
2021-04-21 Testing pressure sensor
2021-05-04 Added async sensor reading
2021-05-04 small fix
2021-05-11 restructure
2021-05-26 test code for pitot tube
2021-05-26 change LoRa to RFD
2021-11-20 total chaos
2021-12-04 pre cold test
2022-01-24 everything
2022-03-20 Adding of a spool class for telemetry
2022-04-10 Minor change
2022-04-24 Correction of the data protocol (header)
2022-04-24 Correction of the checksum
2024-05-18 bajs

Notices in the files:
test/hardware_test_teensy.cpp:
MIT License
Copyright (c) 2020 Association of Engineering Students in Rocketry
parts and their libraries:
SparkFun-Aesthetics: Licensing: Creative Commons ShareAlike 4.0 International - https://creativecommons.org/licenses/by-sa/4.0
